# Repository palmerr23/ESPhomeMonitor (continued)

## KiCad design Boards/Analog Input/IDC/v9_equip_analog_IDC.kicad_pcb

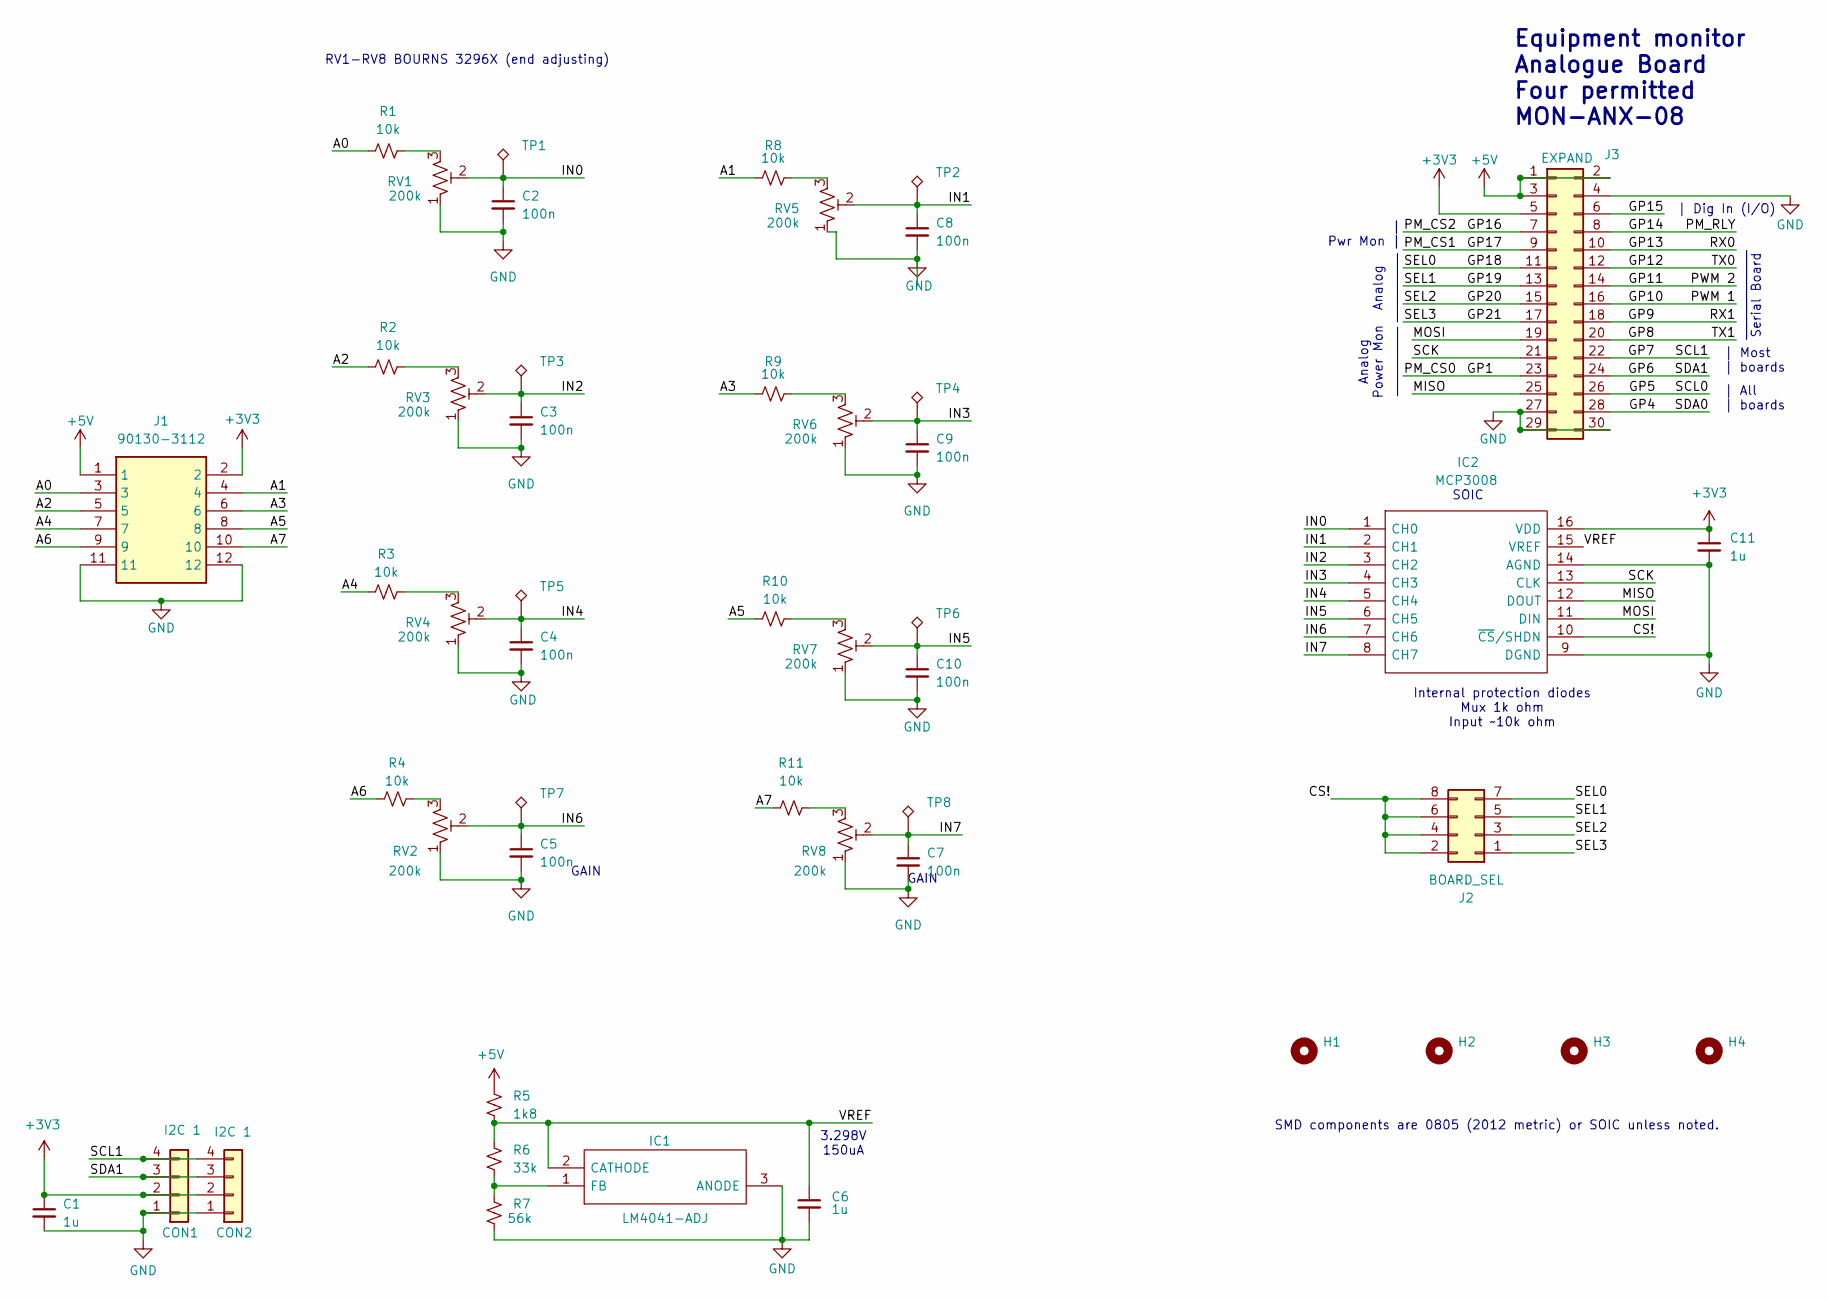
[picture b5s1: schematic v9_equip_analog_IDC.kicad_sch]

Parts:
C1, C6, C11: 1u; C_0805_2012Metric_Pad1.18x1.45mm_HandSolder
C2, C3, C4, C5, C7, C8, C9, C10: 100n; C_0805_2012Metric_Pad1.18x1.45mm_HandSolder
CON1: I2C 1; PinSocket_1x04_P2.54mm_Vertical
CON2: I2C 1; JST_SH_SM04B-SRSS-TB_1x04-1MP_P1.00mm_Horizontal_wide_MP
H1, H2, H3, H4: MountingHole; MountingHole_3.5mm_no_fill
IC1: LM4041-ADJ; SOT95P237X112-3N; Mouser Part Number 595-LM4041C12IDBZR
IC2: MCP3008; SOIC127P600X175-16N; Mouser Part Number 579-MCP3008-I/SL
J1: 90130-3112; SHDRRA12W65P254_2X6_1758X1090X1005P; Mouser Part Number 538-90130-3112
J2: BOARD_SEL; PinHeader_2x04_P2.54mm_Vertical
J3: EXPAND; PinHeader_2x15_P2.54mm_Vertical
R1, R2, R3, R4, R8, R9, R10, R11: 10k; R_0805_2012Metric_Pad1.20x1.40mm_HandSolder
R5: 1k8; R_0805_2012Metric_Pad1.20x1.40mm_HandSolder
R6: 33k; R_0805_2012Metric_Pad1.20x1.40mm_HandSolder
R7: 56k; R_0805_2012Metric_Pad1.20x1.40mm_HandSolder
RV1, RV2, RV3, RV4, RV5, RV6, RV7, RV8: 200k; Potentiometer_Bourns_3296X_Horizontal
TP1, TP2, TP3, TP4, TP5, TP6, TP7, TP8: TestPoint_Alt; TestPoint_THTPad_2.0x2.0mm_Drill1.0mm

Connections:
+3V3: C1.1, C11.1, CON1.2, CON2.2, IC2.16 (VDD), J1.2, J3.5
+5V: J1.1, J3.1, J3.2, J3.3, R5.1
/A0: J1.3, R1.1
/A1: J1.4, R8.1
/A2: J1.5, R2.1
/A3: J1.6, R9.1
/A4: J1.7, R3.1
/A5: J1.8, R10.1
/A6: J1.9, R4.1
/A7: J1.10, R11.1
/CS!: IC2.10 (~CS/SHDN), J2.2, J2.4, J2.6, J2.8
/GP1: J3.23
/GP4: J3.28
/GP5: J3.26
/GP6: CON1.3, CON2.3, J3.24
/GP7: CON1.4, CON2.4, J3.22
/GP8: J3.20
/GP9: J3.18
/GP10: J3.16
/GP11: J3.14
/GP12: J3.12
/GP13: J3.10
/GP14: J3.8
/GP15: J3.6
/GP16: J3.7
/GP17: J3.9
/GP18: J2.7, J3.11
/GP19: J2.5, J3.13
/GP20: J2.3, J3.15
/GP21: J2.1, J3.17
/IN0: C2.1, IC2.1 (CH0), RV1.2, TP1.1
/IN1: C8.1, IC2.2 (CH1), RV5.2, TP2.1
/IN2: C3.1, IC2.3 (CH2), RV3.2, TP3.1
/IN3: C9.1, IC2.4 (CH3), RV6.2, TP4.1
/IN4: C4.1, IC2.5 (CH4), RV4.2, TP5.1
/IN5: C10.1, IC2.6 (CH5), RV7.2, TP6.1
/IN6: C5.1, IC2.7 (CH6), RV2.2, TP7.1
/IN7: C7.1, IC2.8 (CH7), RV8.2, TP8.1
/MISO: IC2.12 (DOUT), J3.25
/MOSI: IC2.11 (DIN), J3.19
/SCK: IC2.13 (CLK), J3.21
/VREF: C6.1, IC1.2 (CATHODE), IC2.15 (VREF), R5.2, R6.1
GND: C1.2, C2.2, C3.2, C4.2, C5.2, C6.2, C7.2, C8.2, C9.2, C10.2, C11.2, CON1.1, CON2.1, IC1.3 (ANODE), IC2.9 (DGND), IC2.14 (AGND), J1.11, J1.12, J3.4, J3.27, J3.29, J3.30, R7.2, RV1.1, RV2.1, RV3.1, RV4.1, RV5.1, RV6.1, RV7.1, RV8.1
unnamed: IC1.1 (FB), R6.2, R7.1
unnamed: R1.2, RV1.3
unnamed: R2.2, RV3.3
unnamed: R3.2, RV4.3
unnamed: R4.2, RV2.3
unnamed: R8.2, RV5.3
unnamed: R9.2, RV6.3
unnamed: R10.2, RV7.3
unnamed: R11.2, RV8.3

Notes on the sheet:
GAIN
| Pwr Mon |
3.298V 150uA
SMD components are 0805 (2012 metric) or SOIC unless noted.
| Dig In (I/O)
Internal protection diodes Mux 1k ohm Input ~10k ohm
_____________ Serial Board
Equipment monitor Analogue Board Four permitted MON-ANX-08
SOIC
Analog Power Mon __________
Analog __________
| Most | boards
RV1-RV8 BOURNS 3296X (end adjusting)
| All | boards

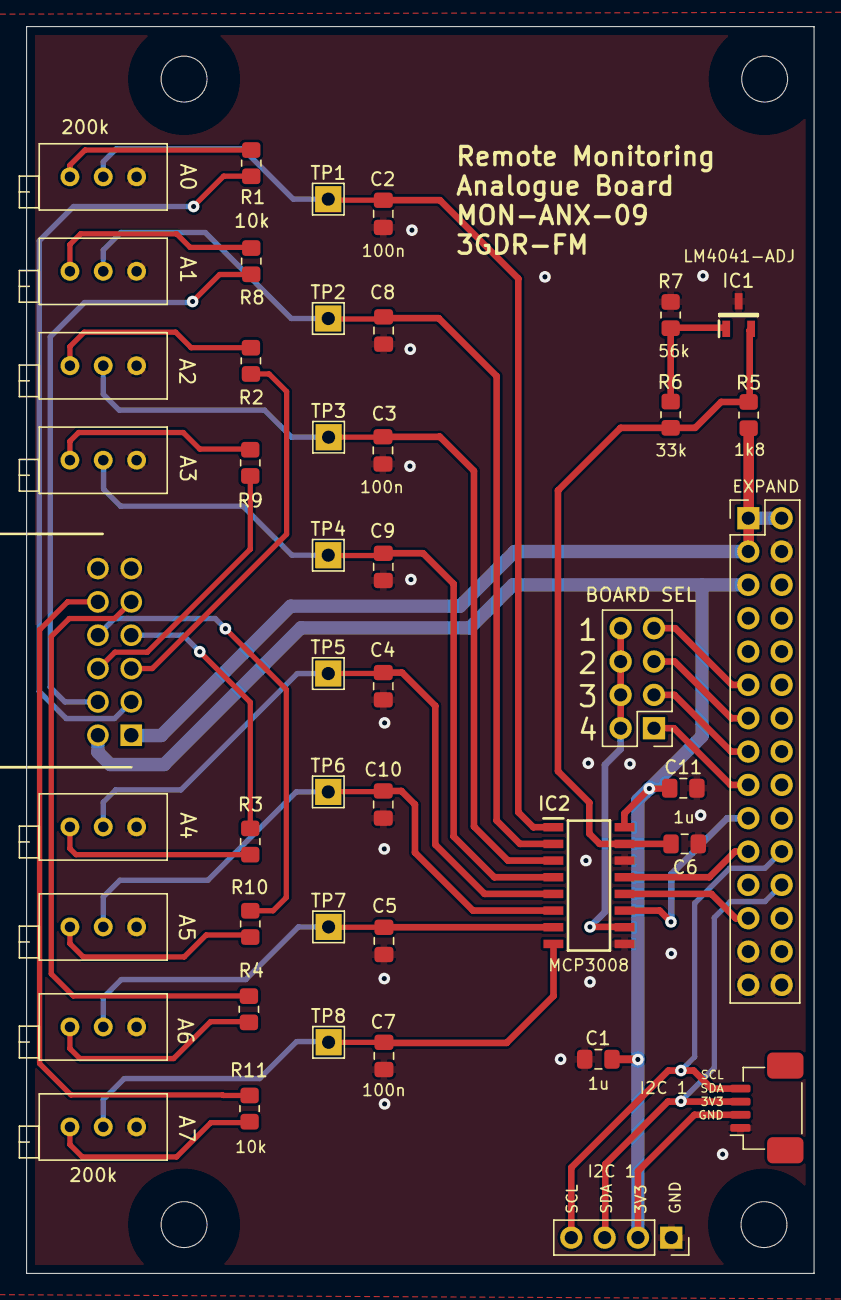
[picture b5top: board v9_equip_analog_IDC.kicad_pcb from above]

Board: 2 copper layers, 60.0 x 95.0 mm, 49 parts (0 on the bottom side), 39 nets.

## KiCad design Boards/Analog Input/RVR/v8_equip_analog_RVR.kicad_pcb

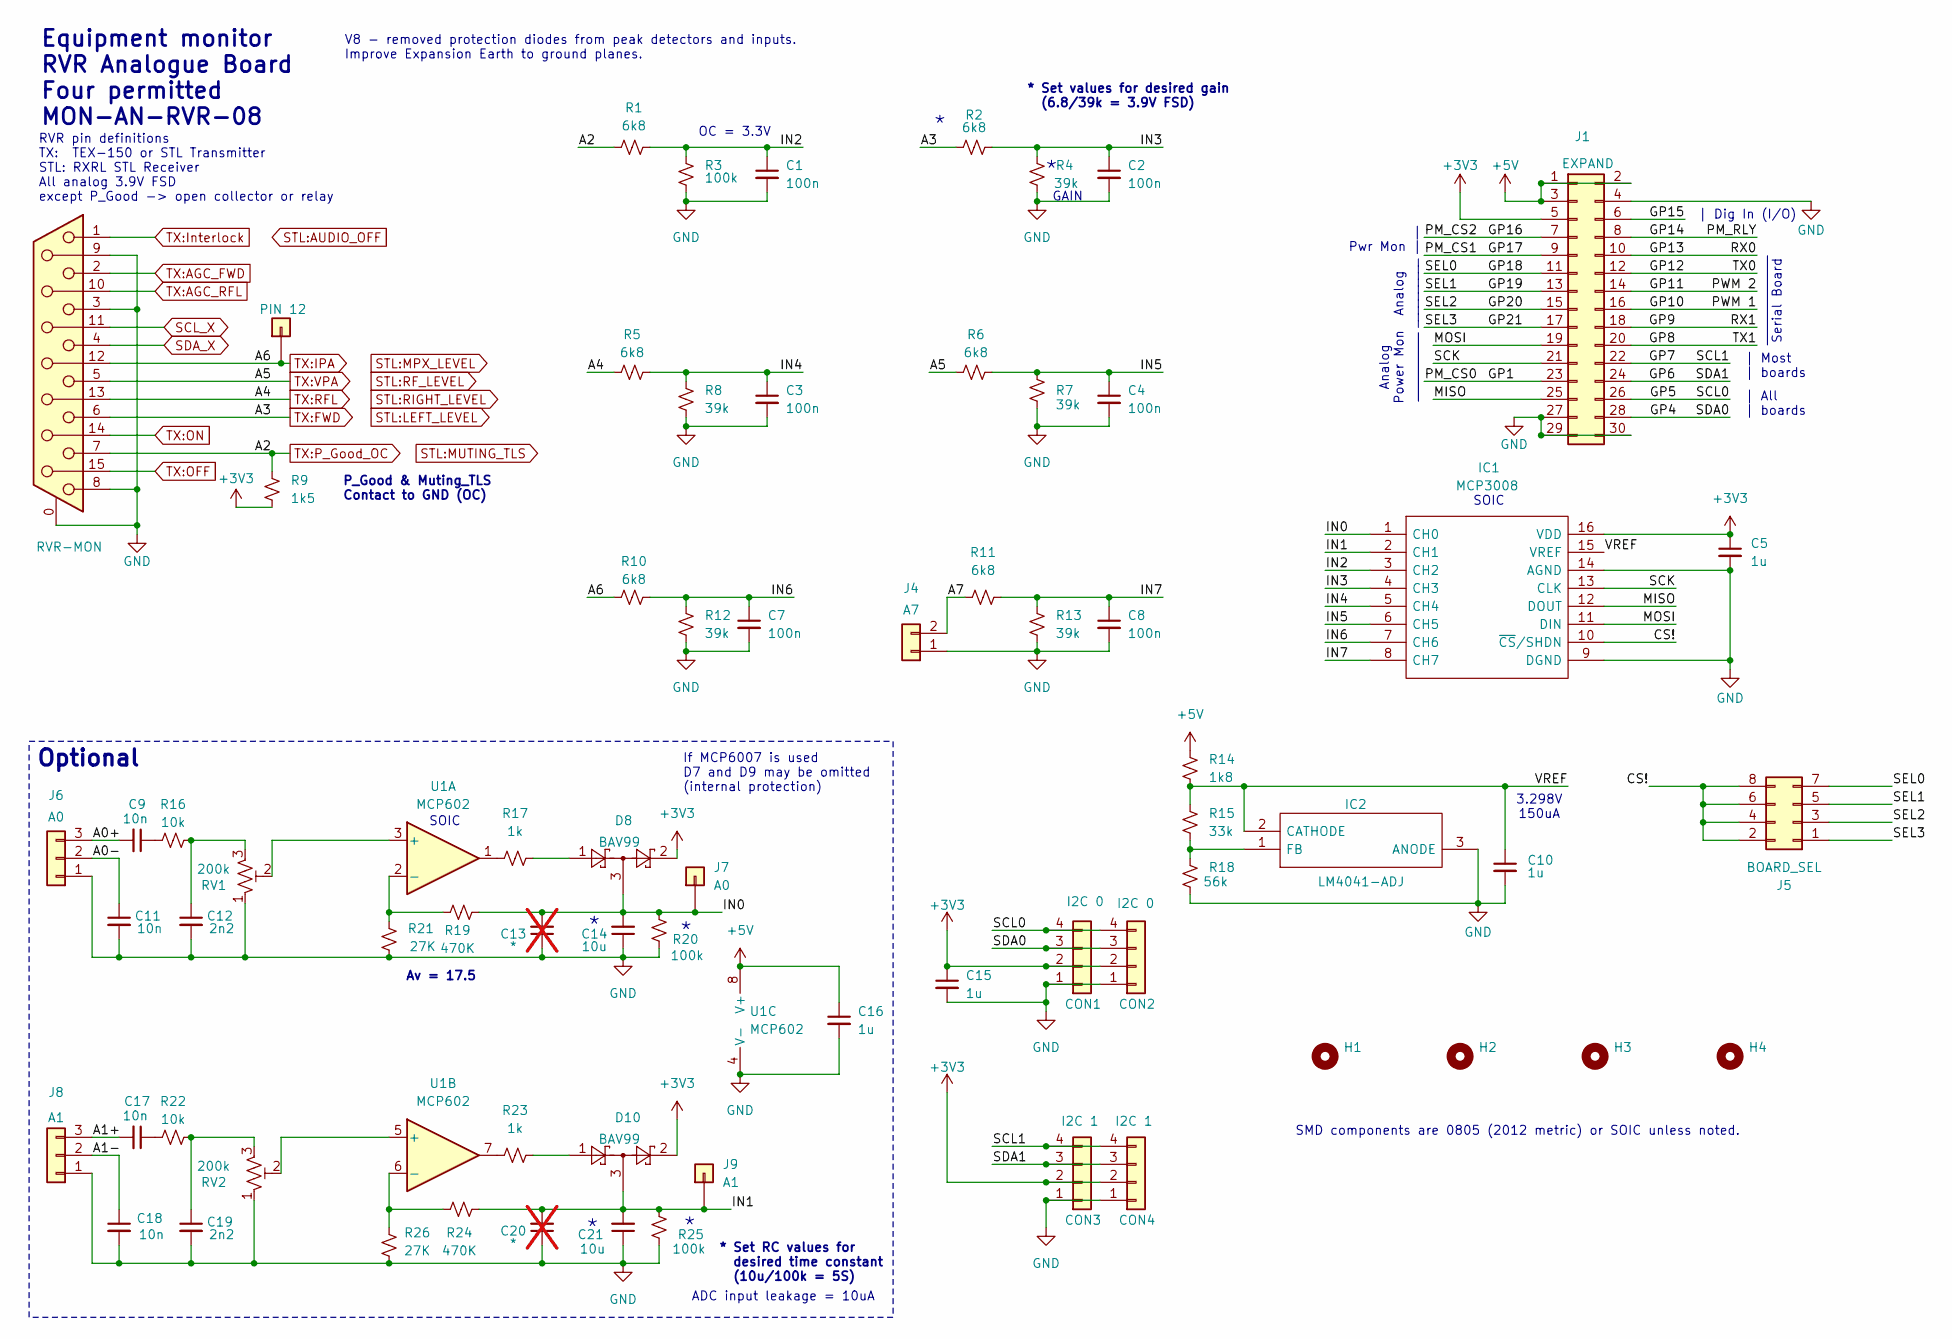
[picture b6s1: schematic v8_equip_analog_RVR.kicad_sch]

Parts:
C1, C2, C3, C4, C7, C8: 100n; C_0805_2012Metric_Pad1.18x1.45mm_HandSolder
C5, C10, C15, C16: 1u; C_0805_2012Metric_Pad1.18x1.45mm_HandSolder
C9, C11, C17, C18: 10n; C_0805_2012Metric_Pad1.18x1.45mm_HandSolder
C12, C19: 2n2; C_0805_2012Metric_Pad1.18x1.45mm_HandSolder
C13, C20: *; C_0805_2012Metric_Pad1.18x1.45mm_HandSolder; not fitted
C14, C21: 10u; C_0805_2012Metric_Pad1.18x1.45mm_HandSolder
CON1: I2C 0; PinSocket_1x04_P2.54mm_Vertical
CON2: I2C 0; JST_SH_SM04B-SRSS-TB_1x04-1MP_P1.00mm_Horizontal_wide_MP
CON3: I2C 1; PinSocket_1x04_P2.54mm_Vertical
CON4: I2C 1; JST_SH_SM04B-SRSS-TB_1x04-1MP_P1.00mm_Horizontal_wide_MP
D8, D10: BAV99; SOT-23
H1, H2, H3, H4: MountingHole; MountingHole_3.5mm_no_fill
IC1: MCP3008; SOIC127P600X175-16N; Mouser Part Number 579-MCP3008-I/SL
IC2: LM4041-ADJ; SOT95P237X112-3N; Mouser Part Number 595-LM4041C12IDBZR
J1: EXPAND; PinHeader_2x15_P2.54mm_Vertical
J2: PIN 12; PinHeader_1x01_P2.54mm_Vertical
J3: RVR-MON; DSUB-15_Female_Horizontal_P2.77x2.84mm_EdgePinOffset4.94mm_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
J4: A7; K2EDG
J5: BOARD_SEL; PinHeader_2x04_P2.54mm_Vertical
J6: A0; K3EDG
J7: A0; PinHeader_1x01_P2.54mm_Vertical
J8: A1; K3EDG
J9: A1; PinHeader_1x01_P2.54mm_Vertical
R1, R2, R5, R6, R10, R11: 6k8; R_0805_2012Metric_Pad1.20x1.40mm_HandSolder
R3, R20, R25: 100k; R_0805_2012Metric_Pad1.20x1.40mm_HandSolder
R4, R7, R8, R12, R13: 39k; R_0805_2012Metric_Pad1.20x1.40mm_HandSolder
R9: 1k5; R_0805_2012Metric_Pad1.20x1.40mm_HandSolder
R14: 1k8; R_0805_2012Metric_Pad1.20x1.40mm_HandSolder
R15: 33k; R_0805_2012Metric_Pad1.20x1.40mm_HandSolder
R16, R22: 10k; R_0805_2012Metric_Pad1.20x1.40mm_HandSolder
R17, R23: 1k; R_0805_2012Metric_Pad1.20x1.40mm_HandSolder
R18: 56k; R_0805_2012Metric_Pad1.20x1.40mm_HandSolder
R19, R24: 470K; R_0805_2012Metric_Pad1.20x1.40mm_HandSolder
R21, R26: 27K; R_0805_2012Metric_Pad1.20x1.40mm_HandSolder
RV1, RV2: 200k; Potentiometer_Bourns_3296X_Horizontal
U1: MCP602; SO-8_3.9x4.9mm_P1.27mm

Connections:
+3V3: C5.1, C15.1, CON1.2, CON2.2, CON3.2, CON4.2, D8.2, D10.2, IC1.16 (VDD), J1.5, R9.1
+5V: C16.1, J1.1, J1.2, J1.3, R14.1, U1.8 (V+)
/A0+: C9.2, J6.3
/A0-: C11.1, J6.2
/A1+: C17.2, J8.3
/A1-: C18.1, J8.2
/A7: J4.2, R11.1
/CS!: IC1.10 (~CS/SHDN), J5.2, J5.4, J5.6, J5.8
/GP1: J1.23
/GP4: CON1.3, CON2.3, J1.28
/GP5: CON1.4, CON2.4, J1.26
/GP6: CON3.3, CON4.3, J1.24
/GP7: CON3.4, CON4.4, J1.22
/GP8: J1.20
/GP9: J1.18
/GP10: J1.16
/GP11: J1.14
/GP12: J1.12
/GP13: J1.10
/GP14: J1.8
/GP15: J1.6
/GP16: J1.7
/GP17: J1.9
/GP18: J1.11, J5.7
/GP19: J1.13, J5.5
/GP20: J1.15, J5.3
/GP21: J1.17, J5.1
/IN0: C13.2, C14.2, D8.3, IC1.1 (CH0), J7.1, R19.2, R20.2
/IN1: C20.2, C21.2, D10.3, IC1.2 (CH1), J9.1, R24.2, R25.2
/IN2: C1.1, IC1.3 (CH2), R1.2, R3.1
/IN3: C2.1, IC1.4 (CH3), R2.2, R4.1
/IN4: C3.1, IC1.5 (CH4), R5.2, R8.1
/IN5: C4.1, IC1.6 (CH5), R6.2, R7.1
/IN6: C7.1, IC1.7 (CH6), R10.2, R12.1
/IN7: C8.1, IC1.8 (CH7), R11.2, R13.1
/MISO: IC1.12 (DOUT), J1.25
/MOSI: IC1.11 (DIN), J1.19
/SCK: IC1.13 (CLK), J1.21
/VREF: C10.1, IC1.15 (VREF), IC2.2 (CATHODE), R14.2, R15.1
GND: C1.2, C2.2, C3.2, C4.2, C5.2, C7.2, C8.2, C10.2, C11.2, C12.2, C13.1, C14.1, C15.2, C16.2, C18.2, C19.2, C20.1, C21.1, CON1.1, CON2.1, CON3.1, CON4.1, IC1.9 (DGND), IC1.14 (AGND), IC2.3 (ANODE), J1.4, J1.27, J1.29, J1.30, J3.0 (PAD), J3.3, J3.8, J3.9, J4.1, J6.1, J8.1, R3.2, R4.2, R7.2, R8.2, R12.2, R13.2, R18.2, R20.1, R21.1, R25.1, R26.1, RV1.1, RV2.1, U1.4 (V-)
unnamed: C9.1, R16.1
unnamed: C12.1, R16.2, RV1.3
unnamed: C17.1, R22.1
unnamed: C19.1, R22.2, RV2.3
unnamed: D8.1, R17.2
unnamed: D10.1, R23.2
unnamed: IC2.1 (FB), R15.2, R18.1
unnamed: R17.1, U1.1
unnamed: R23.1, U1.7
unnamed: RV1.2, U1.3 (+)
unnamed: R19.1, R21.2, U1.2 (-)
unnamed: RV2.2, U1.5 (+)
unnamed: R24.1, R26.2, U1.6 (-)
SCL_X: J3.11 (P111)
SDA_X: J3.4
TX:AGC_FWD: J3.2
TX:AGC_RFL: J3.10
TX:FWD: J3.6, R2.1
TX:IPA: J2.1, J3.12, R10.1
TX:Interlock: J3.1
TX:OFF: J3.15
TX:ON: J3.14
TX:P_Good_OC: J3.7, R1.1, R9.2
TX:RFL: J3.13, R5.1
TX:VPA: J3.5, R6.1

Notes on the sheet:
GAIN
| Pwr Mon |
3.298V 150uA
OC = 3.3V
SOIC
V8 - removed protection diodes from peak detectors and inputs. Improve Expansion Earth to ground planes.
Av = 17.5
SMD components are 0805 (2012 metric) or SOIC unless noted.
| Dig In (I/O)
* Set values for desired gain (6.8/39k = 3.9V FSD)
_____________ Serial Board
P_Good & Muting_TLS Contact to GND (OC)
If MCP6007 is used D7 and D9 may be omitted (internal protection)
Optional
Equipment monitor RVR Analogue Board Four permitted MON-AN-RVR-08
ADC input leakage = 10uA
Analog Power Mon __________
Analog __________
RVR pin definitions TX: TEX-150 or STL Transmitter STL: RXRL STL Receiver All analog 3.9V FSD except P_Good -> open collector or relay
| Most | boards
* Set RC values for desired time constant (10u/100k = 5S)
| All | boards

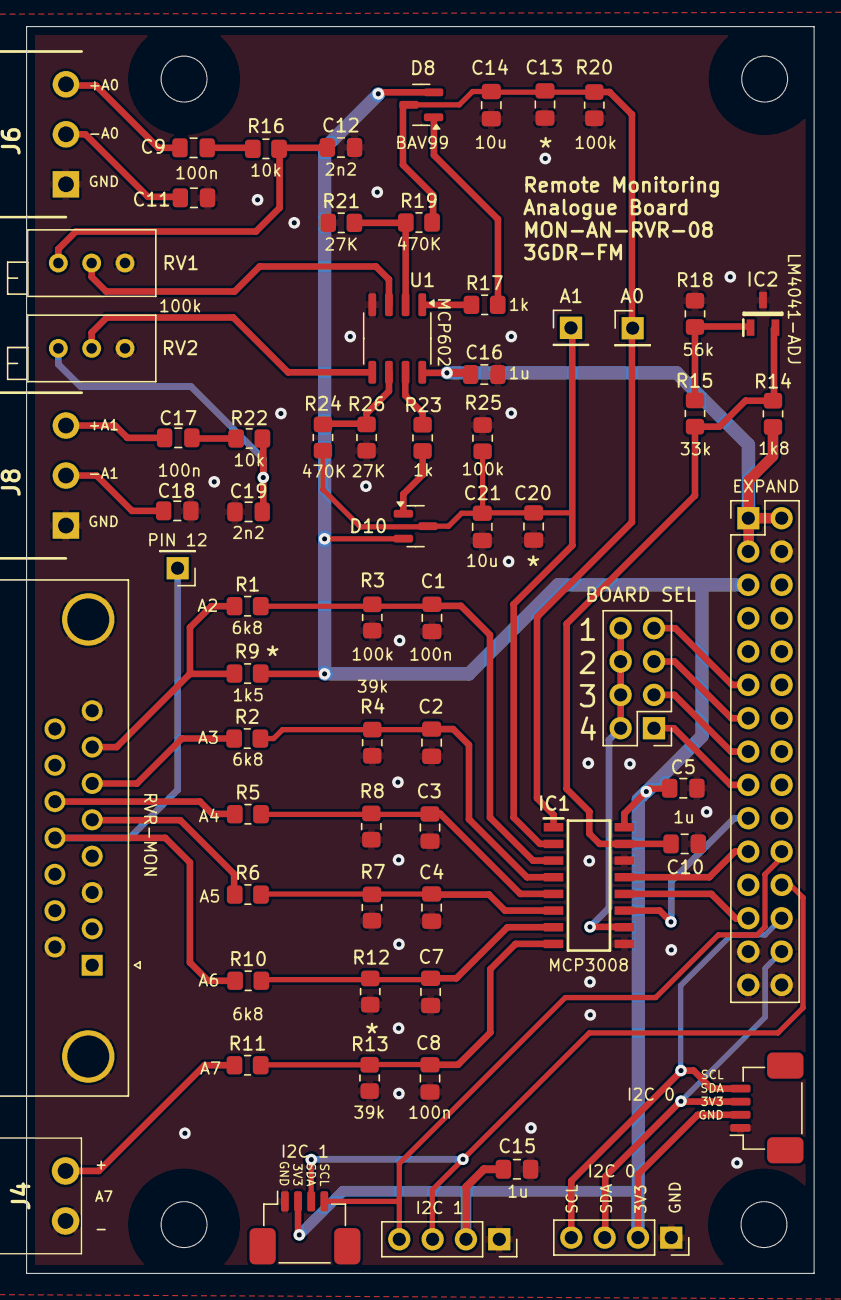
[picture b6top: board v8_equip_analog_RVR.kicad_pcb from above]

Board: 2 copper layers, 60.0 x 95.0 mm, 70 parts (0 on the bottom side), 47 nets.

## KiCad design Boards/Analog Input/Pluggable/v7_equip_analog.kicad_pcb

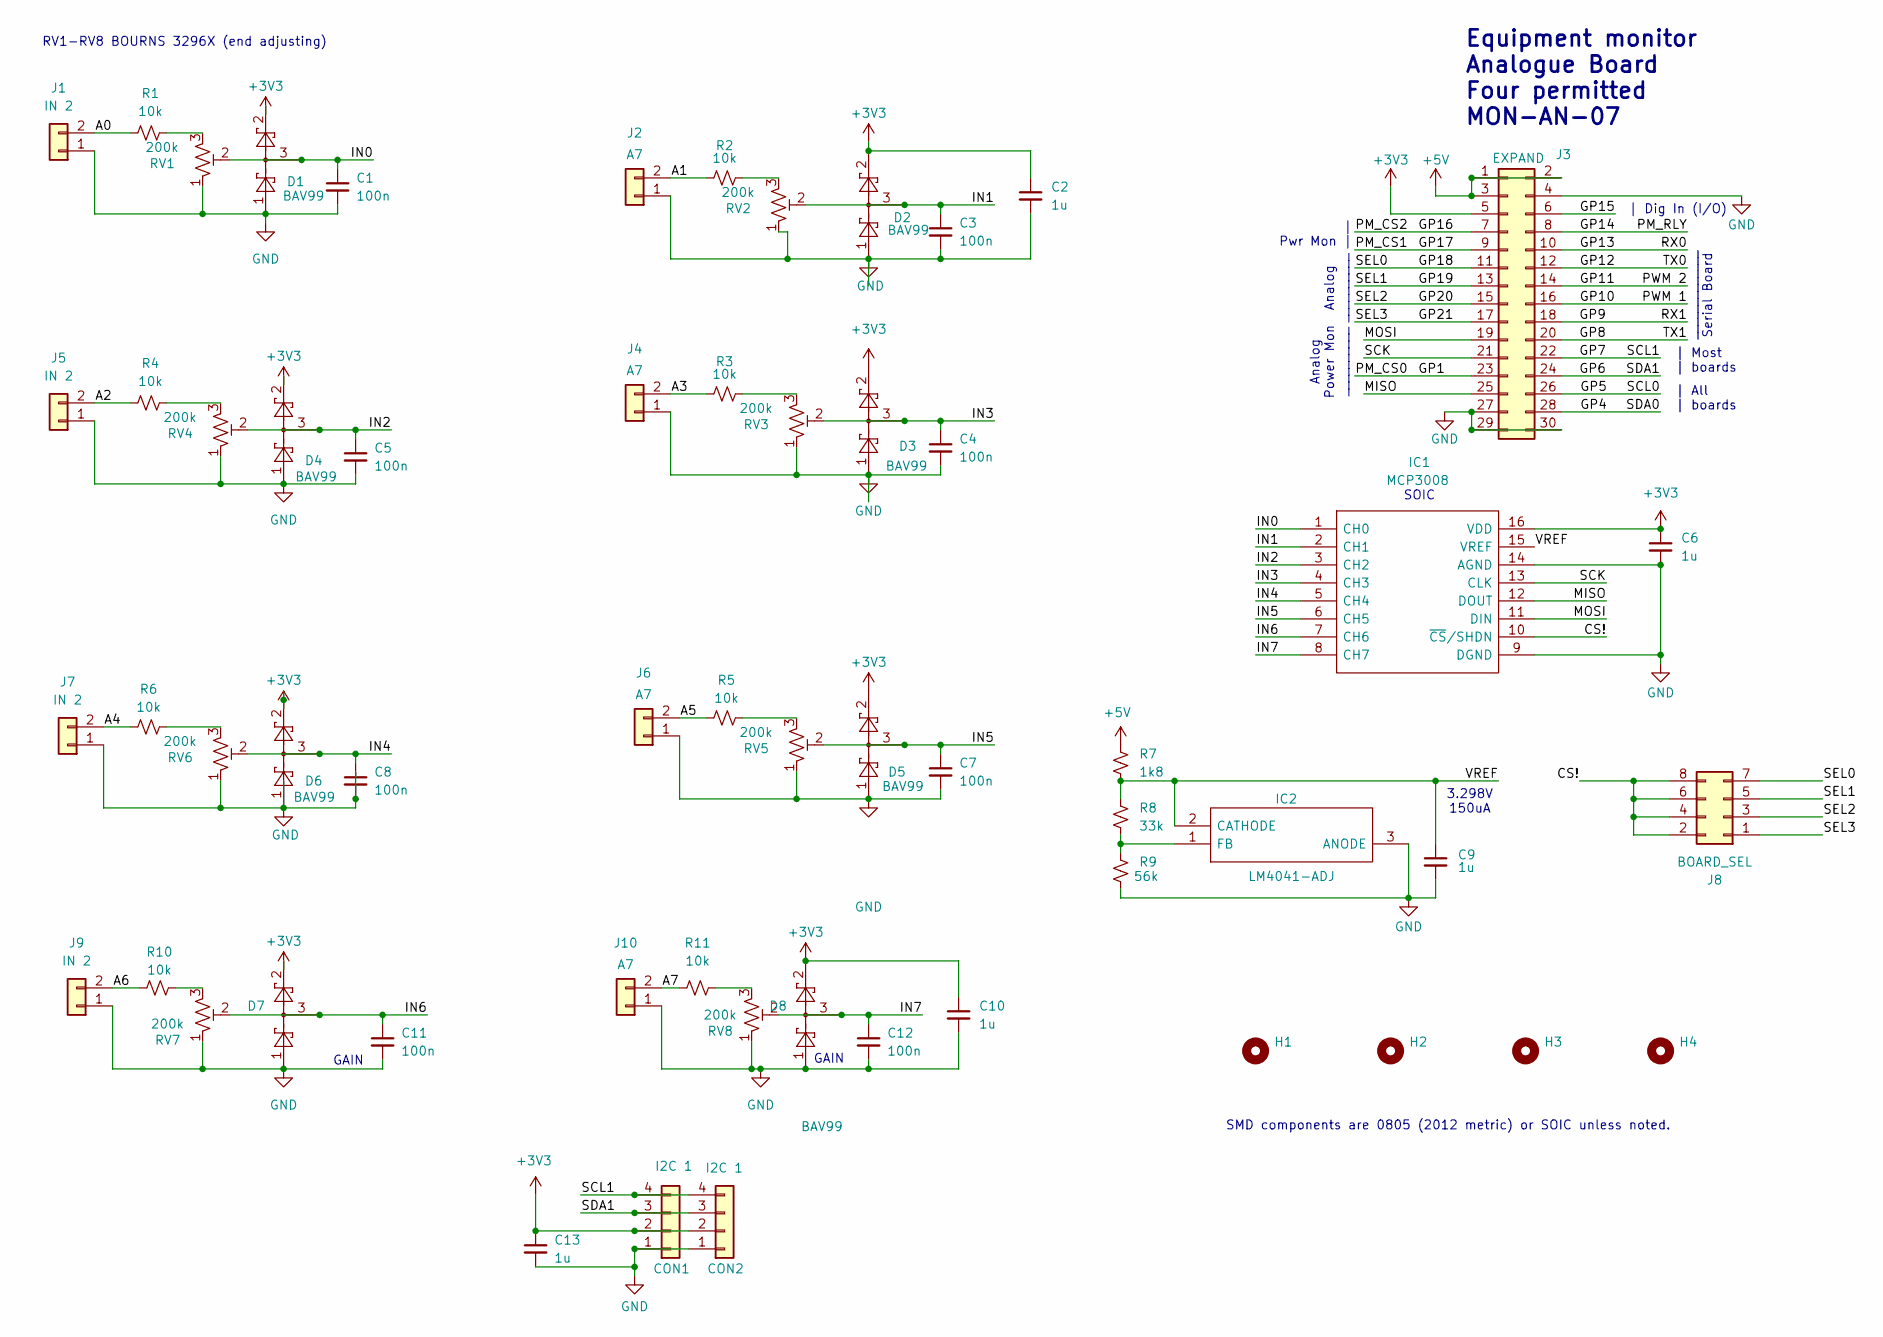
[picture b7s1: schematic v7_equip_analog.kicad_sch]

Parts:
C1, C3, C4, C5, C7, C8, C11, C12: 100n; C_0805_2012Metric_Pad1.18x1.45mm_HandSolder
C2, C6, C9, C10, C13: 1u; C_0805_2012Metric_Pad1.18x1.45mm_HandSolder
CON1: I2C 1; PinSocket_1x04_P2.54mm_Vertical
CON2: I2C 1; JST_SH_SM04B-SRSS-TB_1x04-1MP_P1.00mm_Horizontal_wide_MP
D1, D2, D3, D4, D5, D6, D7, D8: BAV99; SOT-23
H1, H2, H3, H4: MountingHole; MountingHole_3.5mm_no_fill
IC1: MCP3008; SOIC127P600X175-16N; Mouser Part Number 579-MCP3008-I/SL
IC2: LM4041-ADJ; SOT95P237X112-3N; Mouser Part Number 595-LM4041C12IDBZR
J1, J5, J7, J9: IN 2; K2EDG; Mouser Part Number 649-220110-D021A01LF
J2, J4, J6, J10: A7; K2EDG
J3: EXPAND; PinHeader_2x15_P2.54mm_Vertical
J8: BOARD_SEL; PinHeader_2x04_P2.54mm_Vertical
R1, R2, R3, R4, R5, R6, R10, R11: 10k; R_0805_2012Metric_Pad1.20x1.40mm_HandSolder
R7: 1k8; R_0805_2012Metric_Pad1.20x1.40mm_HandSolder
R8: 33k; R_0805_2012Metric_Pad1.20x1.40mm_HandSolder
R9: 56k; R_0805_2012Metric_Pad1.20x1.40mm_HandSolder
RV1, RV2, RV3, RV4, RV5, RV6, RV7, RV8: 200k; Potentiometer_Bourns_3296X_Horizontal

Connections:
+3V3: C2.1, C6.1, C10.1, C13.1, CON1.2, CON2.2, D1.2, D2.2, D3.2, D4.2, D5.2, D6.2, D7.2, D8.2, IC1.16 (VDD), J3.5
+5V: J3.1, J3.2, J3.3, R7.1
/A0: J1.2, R1.1
/A1: J2.2, R2.1
/A2: J5.2, R4.1
/A3: J4.2, R3.1
/A4: J7.2, R6.1
/A5: J6.2, R5.1
/A6: J9.2, R10.1
/A7: J10.2, R11.1
/CS!: IC1.10 (~CS/SHDN), J8.2, J8.4, J8.6, J8.8
/GP1: J3.23
/GP4: J3.28
/GP5: J3.26
/GP6: CON1.3, CON2.3, J3.24
/GP7: CON1.4, CON2.4, J3.22
/GP8: J3.20
/GP9: J3.18
/GP10: J3.16
/GP11: J3.14
/GP12: J3.12
/GP13: J3.10
/GP14: J3.8
/GP15: J3.6
/GP16: J3.7
/GP17: J3.9
/GP18: J3.11, J8.7
/GP19: J3.13, J8.5
/GP20: J3.15, J8.3
/GP21: J3.17, J8.1
/IN0: C1.1, D1.3, IC1.1 (CH0), RV1.2
/IN1: C3.1, D2.3, IC1.2 (CH1), RV2.2
/IN2: C5.1, D4.3, IC1.3 (CH2), RV4.2
/IN3: C4.1, D3.3, IC1.4 (CH3), RV3.2
/IN4: C8.1, D6.3, IC1.5 (CH4), RV6.2
/IN5: C7.1, D5.3, IC1.6 (CH5), RV5.2
/IN6: C11.1, D7.3, IC1.7 (CH6), RV7.2
/IN7: C12.1, D8.3, IC1.8 (CH7), RV8.2
/MISO: IC1.12 (DOUT), J3.25
/MOSI: IC1.11 (DIN), J3.19
/SCK: IC1.13 (CLK), J3.21
/VREF: C9.1, IC1.15 (VREF), IC2.2 (CATHODE), R7.2, R8.1
GND: C1.2, C2.2, C3.2, C4.2, C5.2, C6.2, C7.2, C8.2, C9.2, C10.2, C11.2, C12.2, C13.2, CON1.1, CON2.1, D1.1, D2.1, D3.1, D4.1, D5.1, D6.1, D7.1, D8.1, IC1.9 (DGND), IC1.14 (AGND), IC2.3 (ANODE), J1.1, J2.1, J3.4, J3.27, J3.29, J3.30, J4.1, J5.1, J6.1, J7.1, J9.1, J10.1, R9.2, RV1.1, RV2.1, RV3.1, RV4.1, RV5.1, RV6.1, RV7.1, RV8.1
unnamed: IC2.1 (FB), R8.2, R9.1
unnamed: R1.2, RV1.3
unnamed: R2.2, RV2.3
unnamed: R3.2, RV3.3
unnamed: R4.2, RV4.3
unnamed: R5.2, RV5.3
unnamed: R6.2, RV6.3
unnamed: R10.2, RV7.3
unnamed: R11.2, RV8.3

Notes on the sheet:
GAIN
| Pwr Mon |
3.298V 150uA
SMD components are 0805 (2012 metric) or SOIC unless noted.
| Dig In (I/O)
_____________ Serial Board
Equipment monitor Analogue Board Four permitted MON-AN-07
SOIC
Analog Power Mon __________
Analog __________
| Most | boards
RV1-RV8 BOURNS 3296X (end adjusting)
| All | boards

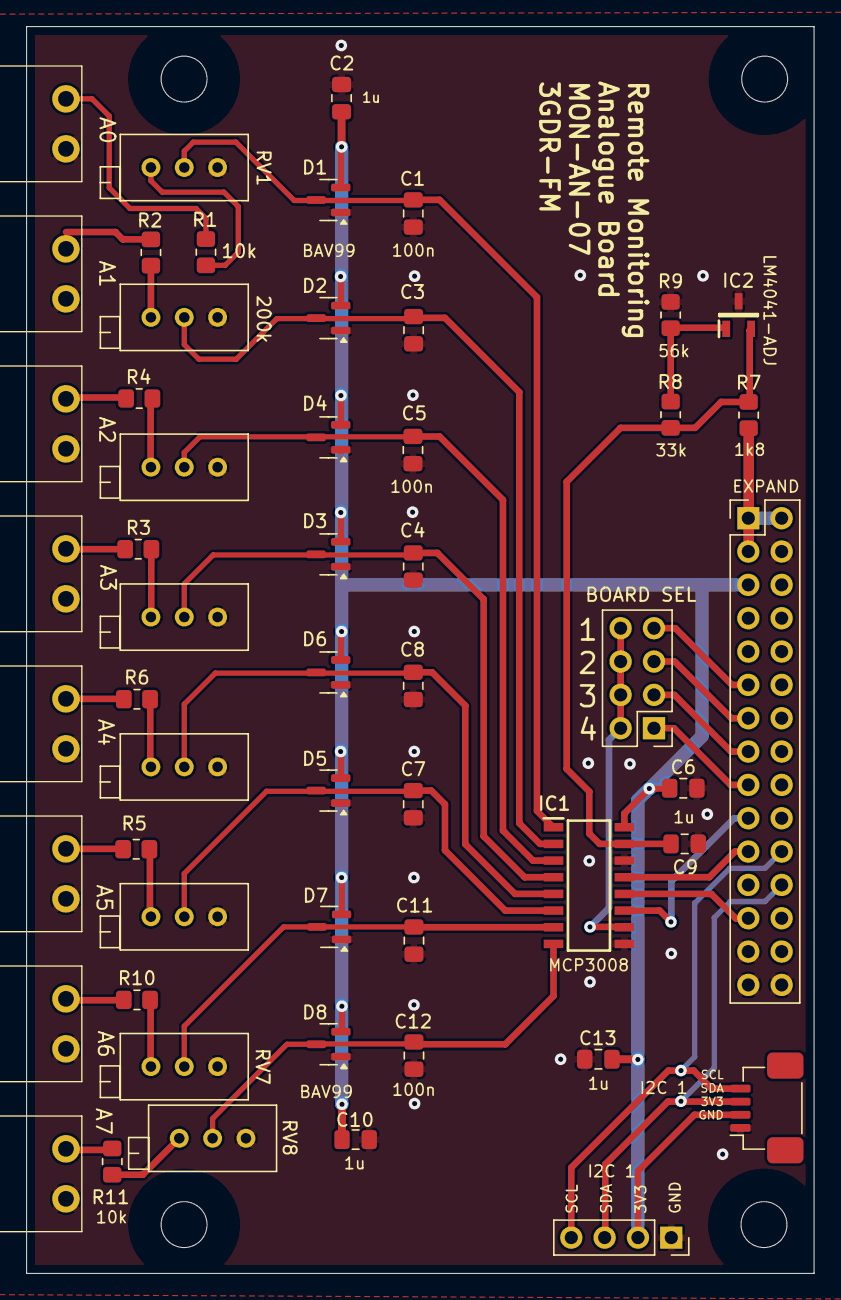
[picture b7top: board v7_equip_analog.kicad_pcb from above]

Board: 2 copper layers, 60.0 x 95.0 mm, 58 parts (0 on the bottom side), 39 nets.

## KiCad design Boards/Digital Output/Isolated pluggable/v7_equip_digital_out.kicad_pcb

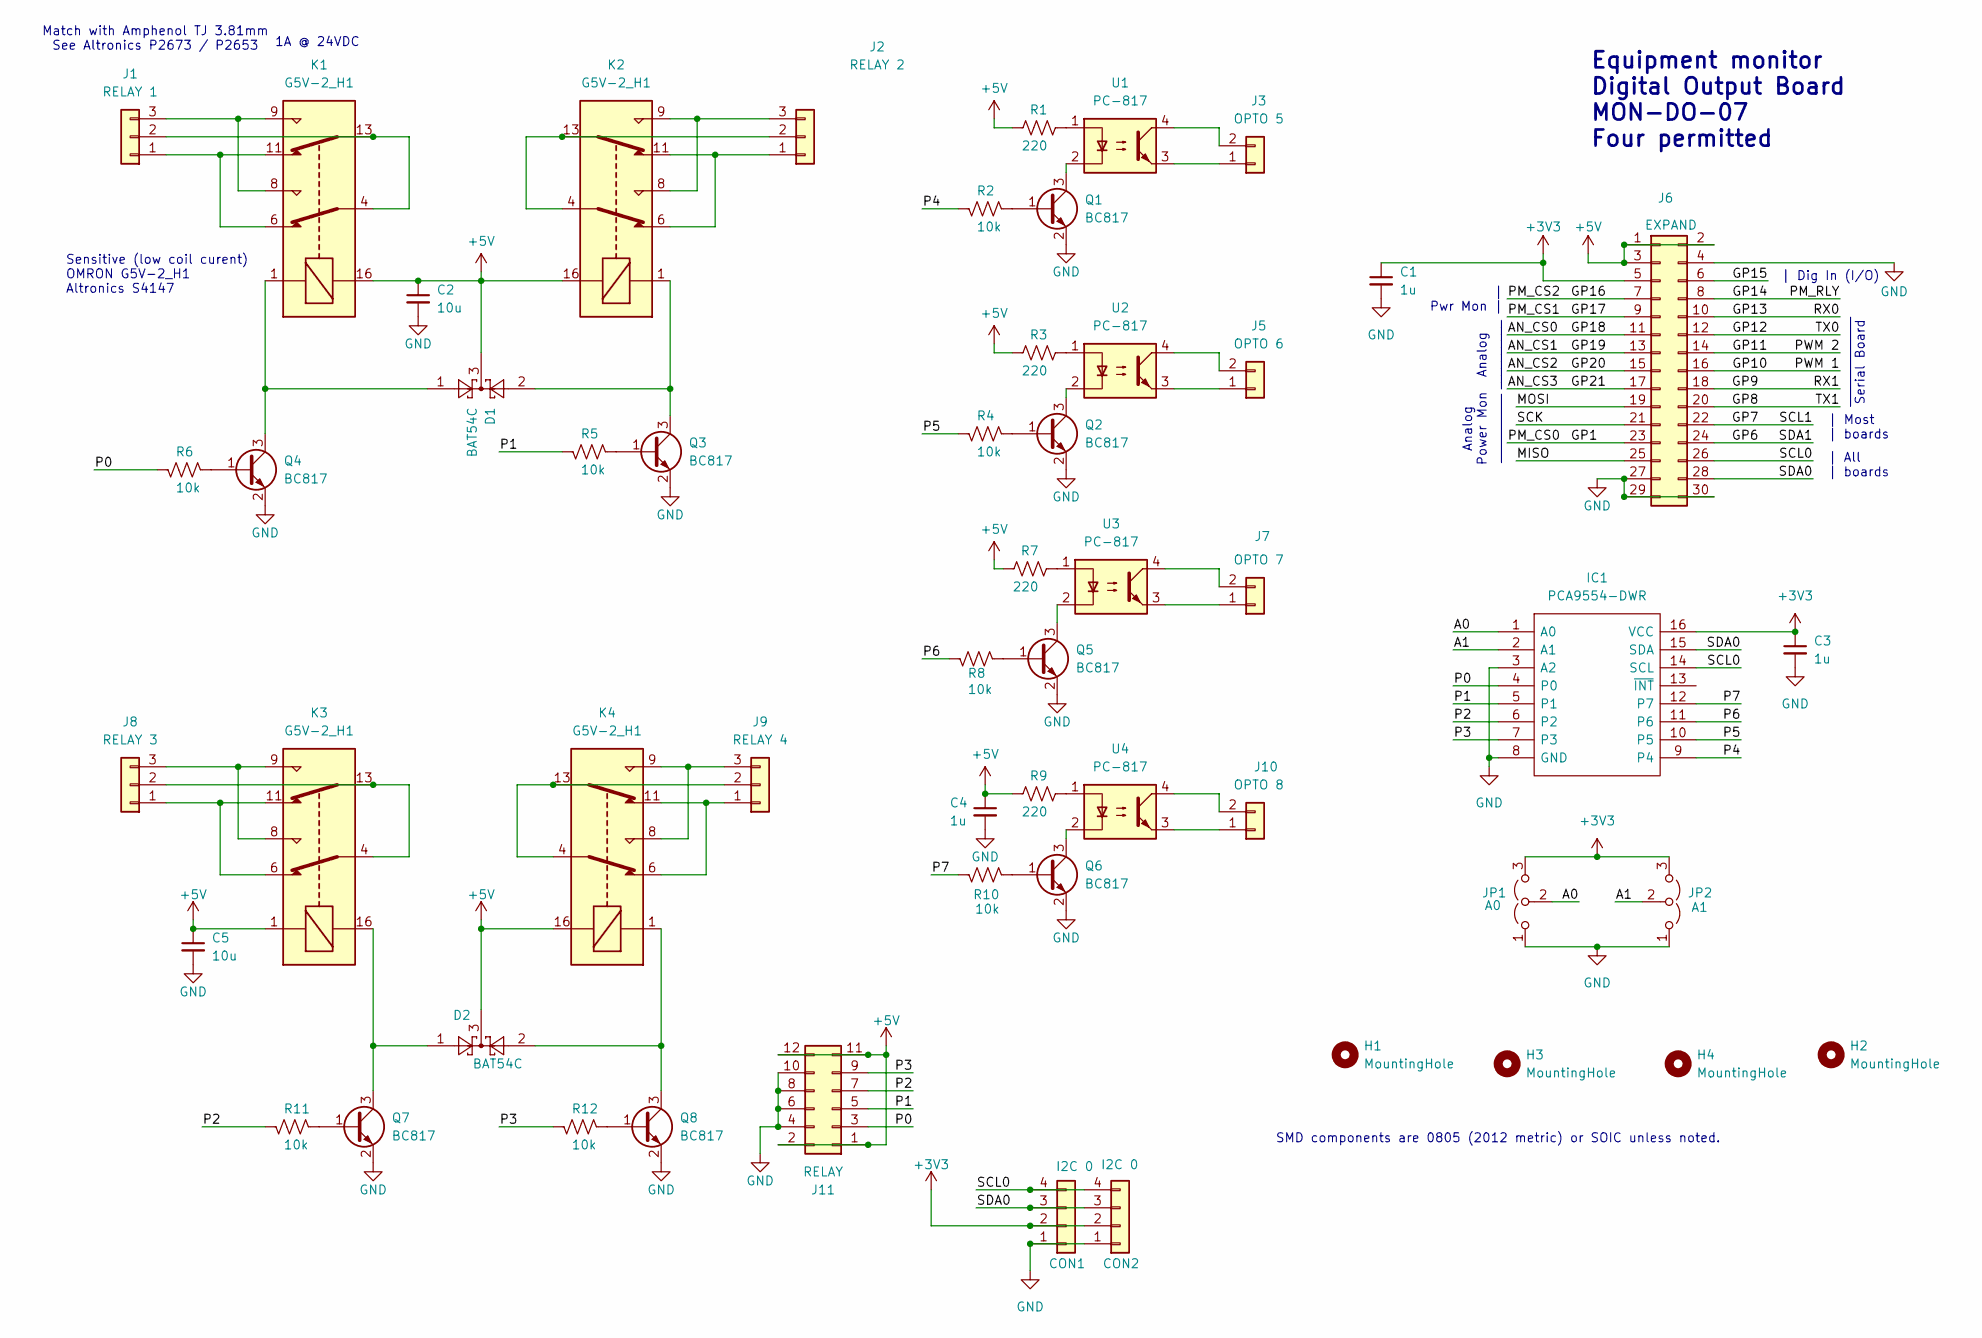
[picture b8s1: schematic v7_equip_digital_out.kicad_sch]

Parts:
C1, C3, C4: 1u; C_0805_2012Metric_Pad1.18x1.45mm_HandSolder
C2, C5: 10u; C_0805_2012Metric_Pad1.18x1.45mm_HandSolder
CON1: I2C 0; PinSocket_1x04_P2.54mm_Vertical
CON2: I2C 0; JST_SH_SM04B-SRSS-TB_1x04-1MP_P1.00mm_Horizontal_wide_MP
D1, D2: BAT54C; SOT-23
H1, H2, H3, H4: MountingHole; MountingHole_3.5mm_no_fill
IC1: PCA9554-DWR; SOIC127P1030X265-16N; Mouser Part Number 595-PCA9534DWR
J1: RELAY 1; K3EDG; Mouser Part Number 649-220110-D031A01LF
J2: RELAY 2; K3EDG; Mouser Part Number 649-220110-D031A01LF
J3: OPTO 5; K2EDG; Mouser Part Number 649-220110-D021A01LF
J5: OPTO 6; K2EDG; Mouser Part Number 649-220110-D021A01LF
J6: EXPAND; PinHeader_2x15_P2.54mm_Vertical
J7: OPTO 7; K2EDG; Mouser Part Number 649-220110-D021A01LF
J8: RELAY 3; K3EDG; Mouser Part Number 649-220110-D031A01LF
J9: RELAY 4; K3EDG; Mouser Part Number 649-220110-D031A01LF
J10: OPTO 8; K2EDG; Mouser Part Number 649-220110-D021A01LF
J11: RELAY; PinHeader_2x06_P2.54mm_Vertical
JP1: A0; PinHeader_1x03_P2.54mm_Vertical
JP2: A1; PinHeader_1x03_P2.54mm_Vertical
K1, K2, K3, K4: G5V-2_H1; Relay_DPDT_Omron_G5V-2_BIGGER_HOLES
Q1, Q2, Q3, Q4, Q5, Q6, Q7, Q8: BC817; SOT-23
R1, R3, R7, R9: 220; R_0805_2012Metric_Pad1.20x1.40mm_HandSolder
R2, R4, R5, R6, R8, R10, R11, R12: 10k; R_0805_2012Metric_Pad1.20x1.40mm_HandSolder
U1, U2, U3, U4: PC-817; SOP254P960X420-4N

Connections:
+3V3: C1.1, C3.1, CON1.2, CON2.2, IC1.16 (VCC), J6.5, JP1.3 (B), JP2.3 (B)
+5V: C2.1, C4.1, C5.1, D1.3, D2.3, J6.1, J6.2, J6.3, J11.1, J11.2, J11.11, J11.12, K1.16, K2.16, K3.1, K4.16, R1.2, R3.2, R7.2, R9.2
/A0: IC1.1 (A0), JP1.2 (C)
/A1: IC1.2 (A1), JP2.2 (C)
/AN_CS0: J6.11
/AN_CS1: J6.13
/AN_CS2: J6.15
/AN_CS3: J6.17
/GP1: J6.23
/GP6: J6.24
/GP7: J6.22
/GP8: J6.20
/GP9: J6.18
/GP10: J6.16
/GP11: J6.14
/GP12: J6.12
/GP13: J6.10
/GP14: J6.8
/GP15: J6.6
/GP16: J6.7
/GP17: J6.9
/MISO: J6.25
/MOSI: J6.19
/P0: IC1.4 (P0), J11.3, R6.1
/P1: IC1.5 (P1), J11.5, R5.1
/P2: IC1.6 (P2), J11.7, R11.1
/P3: IC1.7 (P3), J11.9, R12.1
/P4: IC1.9 (P4), R2.1
/P5: IC1.10 (P5), R4.1
/P6: IC1.11 (P6), R8.1
/P7: IC1.12 (P7), R10.1
/SCK: J6.21
/SCL0: CON1.4, CON2.4, IC1.14 (SCL), J6.26
/SDA0: CON1.3, CON2.3, IC1.15 (SDA), J6.28
GND: C1.2, C2.2, C3.2, C4.2, C5.2, CON1.1, CON2.1, IC1.3 (A2), IC1.8 (GND), J6.4, J6.27, J6.29, J6.30, J11.4, J11.6, J11.8, J11.10, JP1.1 (A), JP2.1 (A), Q1.2 (E), Q2.2 (E), Q3.2 (E), Q4.2 (E), Q5.2 (E), Q6.2 (E), Q7.2 (E), Q8.2 (E)
unnamed: J1.1, K1.6, K1.11
unnamed: J1.2, K1.4, K1.13
unnamed: J1.3, K1.8, K1.9
unnamed: J2.1, K2.6, K2.11
unnamed: J2.2, K2.4, K2.13
unnamed: J2.3, K2.8, K2.9
unnamed: J3.1, U1.3
unnamed: J3.2, U1.4
unnamed: J5.1, U2.3
unnamed: J5.2, U2.4
unnamed: J7.1, U3.3
unnamed: J7.2, U3.4
unnamed: J8.1, K3.6, K3.11
unnamed: J8.2, K3.4, K3.13
unnamed: J8.3, K3.8, K3.9
unnamed: J9.1, K4.6, K4.11
unnamed: J9.2, K4.4, K4.13
unnamed: J9.3, K4.8, K4.9
unnamed: J10.1, U4.3
unnamed: J10.2, U4.4
unnamed: Q1.1 (B), R2.2
unnamed: Q1.3 (C), U1.2
unnamed: Q2.1 (B), R4.2
unnamed: Q2.3 (C), U2.2
unnamed: Q3.1 (B), R5.2
unnamed: D1.2, K2.1, Q3.3 (C)
unnamed: Q4.1 (B), R6.2
unnamed: D1.1, K1.1, Q4.3 (C)
unnamed: Q5.1 (B), R8.2
unnamed: Q5.3 (C), U3.2
unnamed: Q6.1 (B), R10.2
unnamed: Q6.3 (C), U4.2
unnamed: Q7.1 (B), R11.2
unnamed: D2.1, K3.16, Q7.3 (C)
unnamed: Q8.1 (B), R12.2
unnamed: D2.2, K4.1, Q8.3 (C)
unnamed: R1.1, U1.1
unnamed: R3.1, U2.1
unnamed: R7.1, U3.1
unnamed: R9.1, U4.1

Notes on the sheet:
| Dig In (I/O)
Analog __________
1A @ 24VDC
| Pwr Mon |
Match with Amphenol TJ 3.81mm See Altronics P2673 / P2653
Equipment monitor Digital Output Board MON-DO-07 Four permitted
Sensitive (low coil curent) OMRON G5V-2_H1 Altronics S4147
| All | boards
SMD components are 0805 (2012 metric) or SOIC unless noted.
| Most | boards
Analog Power Mon __________
_____________ Serial Board
